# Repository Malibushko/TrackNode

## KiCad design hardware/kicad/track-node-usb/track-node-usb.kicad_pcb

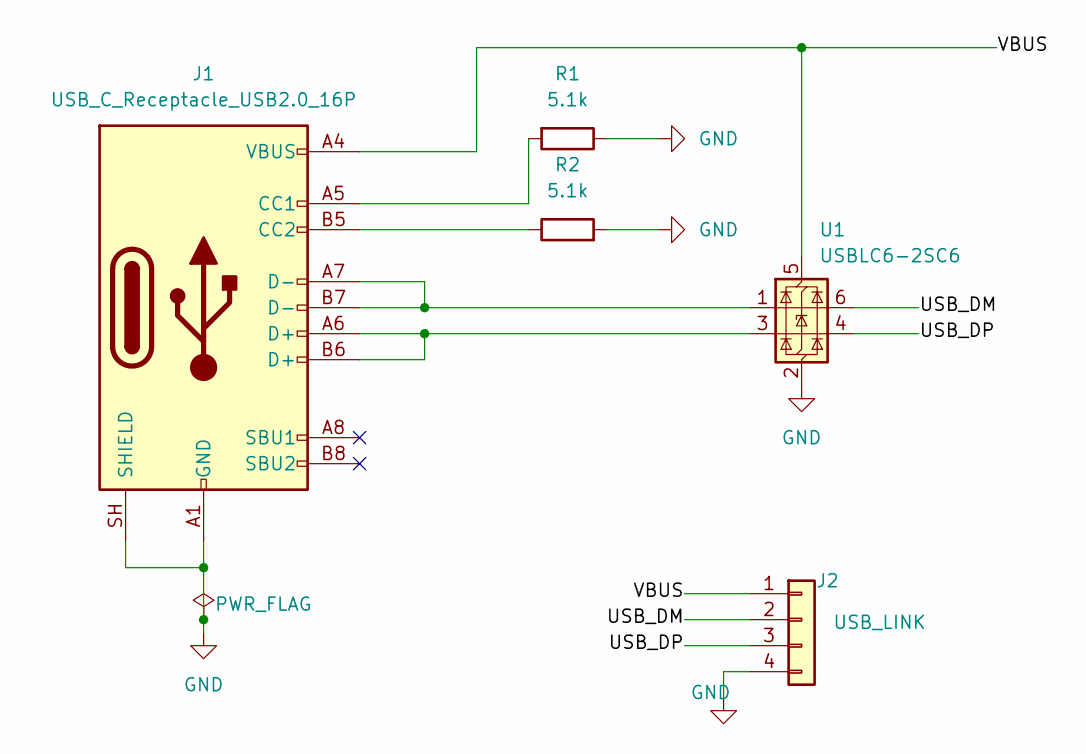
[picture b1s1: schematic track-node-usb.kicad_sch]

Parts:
J1: USB_C_Receptacle_USB2.0_16P; USB_C_Receptacle_HRO_TYPE-C-31-M-12_Edge; LCSC C165948
J2: USB_LINK; JST_SH_SM04B-SRSS-TB_1x04-1MP_P1.00mm_Horizontal; LCSC C160404
R1, R2: 5.1k; R_0603_1608Metric; LCSC C23186
U1: USBLC6-2SC6; SOT-23-6; LCSC C7519

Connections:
/USB_DM: J2.2, U1.6 (I/O1)
/USB_DP: J2.3, U1.4 (I/O2)
/VBUS: J1.A4 (VBUS), J1.A9 (VBUS), J1.B4 (VBUS), J1.B9 (VBUS), J2.1, U1.5 (VBUS)
GND: J1.A1 (GND), J1.A12 (GND), J1.B1 (GND), J1.B12 (GND), J1.SH (SHIELD), J2.4, R1.1, R2.2, U1.2 (GND)
unnamed: J1.A5 (CC1), R1.2
unnamed: J1.B5 (CC2), R2.1
unnamed: J1.A6 (D+), J1.B6 (D+), U1.3 (I/O2)
unnamed: J1.A7 (D-), J1.B7 (D-), U1.1 (I/O1)

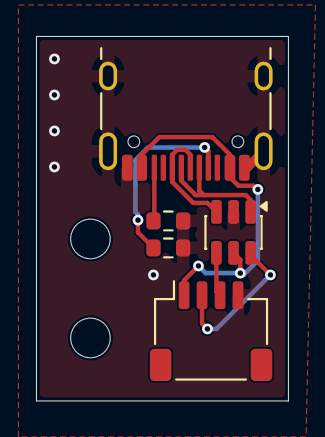
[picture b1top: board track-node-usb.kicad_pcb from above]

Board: 2 copper layers, 14.0 x 20.2 mm, 5 parts (0 on the bottom side), 8 nets.

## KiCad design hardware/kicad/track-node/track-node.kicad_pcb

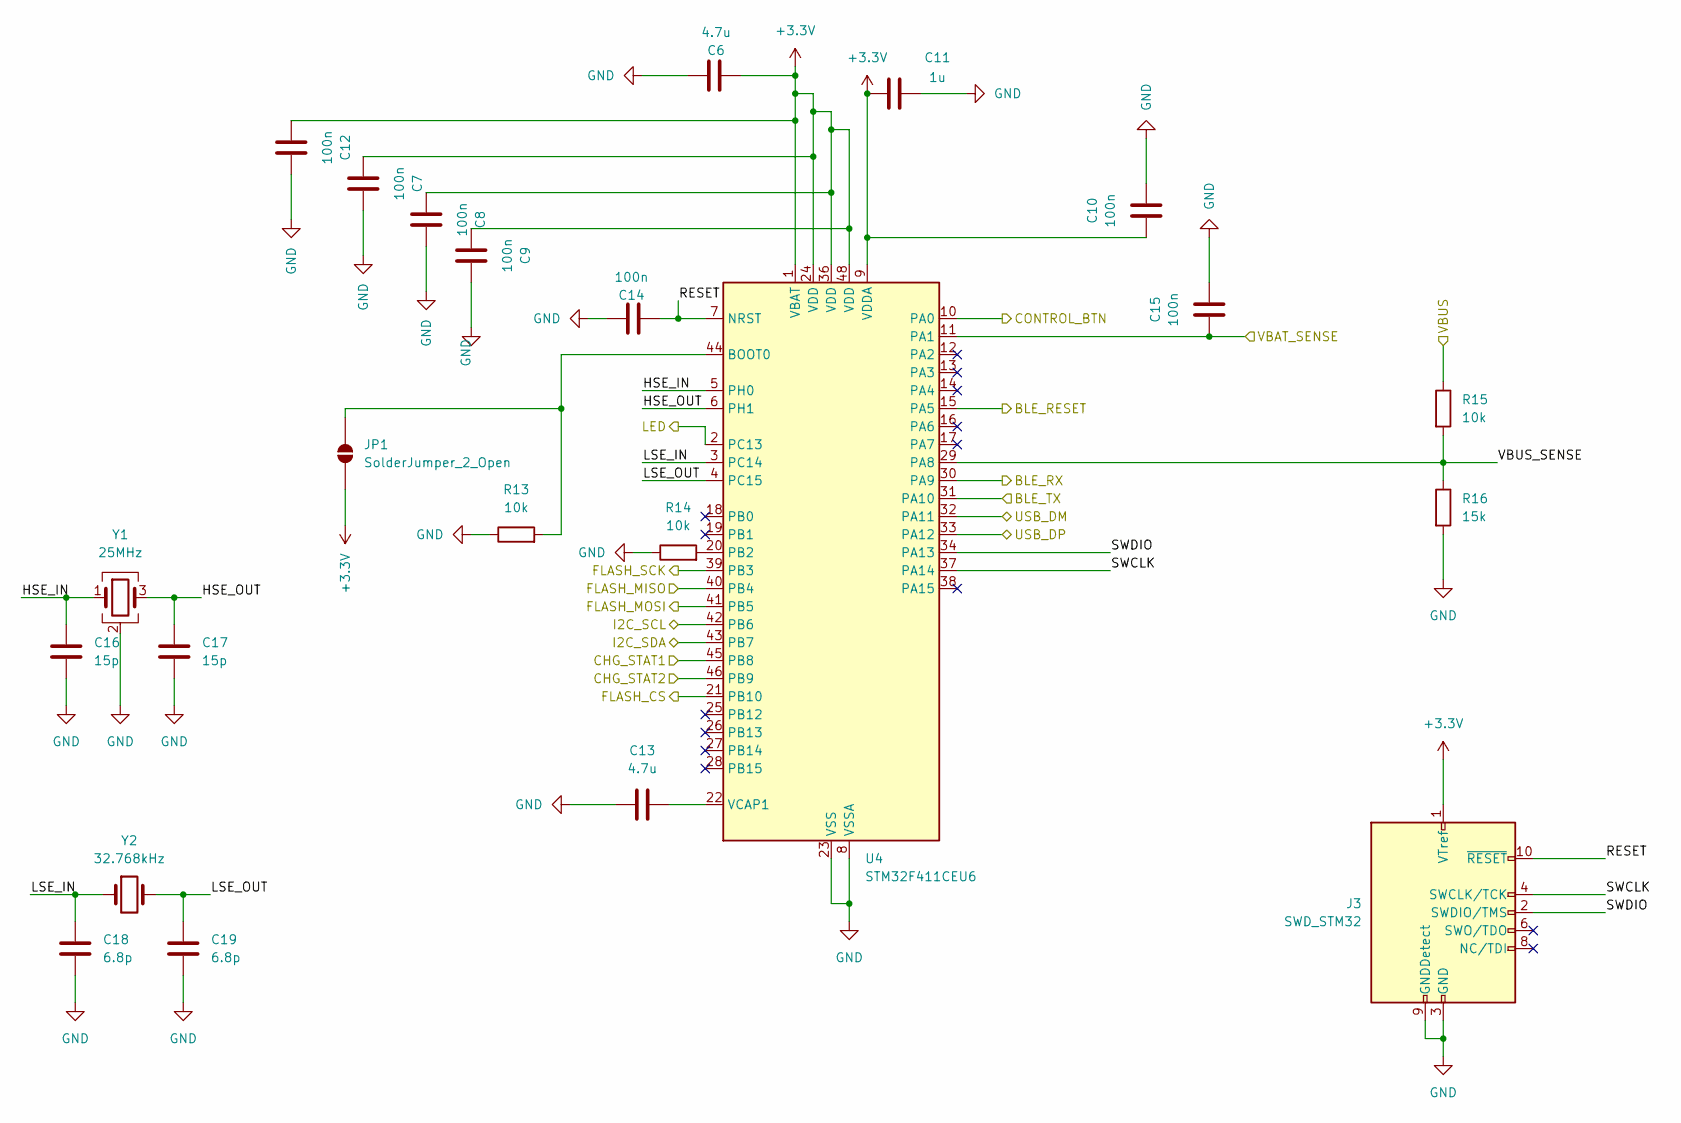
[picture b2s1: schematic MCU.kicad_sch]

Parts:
C6, C13: 4.7u; C_0603_1608Metric; LCSC C19666
C7, C8, C9, C10, C12, C14, C15: 100n; C_0603_1608Metric; LCSC C14663
C11: 1u; C_0603_1608Metric; LCSC C15849
C16, C17: 15p; C_0603_1608Metric; LCSC C1644
C18, C19: 6.8p; C_0603_1608Metric; LCSC C1679
J3: SWD_STM32; HDR-SMD_10P-P1.27-V-M-R2-C5-S1.27-LS5.5; LCSC C598540
JP1: SolderJumper_2_Open; SolderJumper-2_P1.3mm_Open_RoundedPad1.0x1.5mm
R13, R14, R15: 10k; R_0603_1608Metric; LCSC C25804
R16: 15k; R_0603_1608Metric; LCSC C22809
U4: STM32F411CEU6; QFN-48-1EP_7x7mm_P0.5mm_EP5.6x5.6mm; LCSC C60420
Y1: 25MHz; Crystal_SMD_3225-4Pin_3.2x2.5mm; LCSC C9006
Y2: 32.768kHz; Crystal_SMD_3215-2Pin_3.2x1.5mm; LCSC C276424

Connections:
+3.3V: C6.2, C7.2, C8.2, C9.2, C10.2, C11.2, C12.2, J3.1 (VTref), JP1.1 (A), U4.1 (VBAT), U4.9 (VDDA), U4.24 (VDD), U4.36 (VDD), U4.48 (VDD); also elsewhere on the board
/BLE/BLE_RESET: U4.15 (PA5); also elsewhere on the board
/BLE/BLE_RX: U4.30 (PA9); also elsewhere on the board
/BLE/BLE_TX: U4.31 (PA10); also elsewhere on the board
/MCU/CHG_STAT1: U4.45 (PB8); also elsewhere on the board
/MCU/CHG_STAT2: U4.46 (PB9); also elsewhere on the board
/MCU/CONTROL_BTN: U4.10 (PA0); also elsewhere on the board
/MCU/FLASH_CS: U4.21 (PB10); also elsewhere on the board
/MCU/FLASH_MISO: U4.40 (PB4); also elsewhere on the board
/MCU/FLASH_MOSI: U4.41 (PB5); also elsewhere on the board
/MCU/FLASH_SCK: U4.39 (PB3); also elsewhere on the board
/MCU/HSE_IN: C16.1, U4.5 (PH0), Y1.1
/MCU/HSE_OUT: C17.1, U4.6 (PH1), Y1.3
/MCU/I2C_SCL: U4.42 (PB6); also elsewhere on the board
/MCU/I2C_SDA: U4.43 (PB7); also elsewhere on the board
/MCU/LED: U4.2 (PC13); also elsewhere on the board
/MCU/LSE_IN: C18.1, U4.3 (PC14), Y2.1
/MCU/LSE_OUT: C19.1, U4.4 (PC15), Y2.2
/MCU/RESET: C14.2, J3.10 (~RESET), U4.7 (NRST)
/MCU/SWCLK: J3.4 (SWCLK/TCK), U4.37 (PA14)
/MCU/SWDIO: J3.2 (SWDIO/TMS), U4.34 (PA13)
/MCU/USB_DM: U4.32 (PA11); also elsewhere on the board
/MCU/USB_DP: U4.33 (PA12); also elsewhere on the board
/MCU/VBAT_SENSE: C15.2, U4.11 (PA1); also elsewhere on the board
/MCU/VBUS: R15.1; also elsewhere on the board
/MCU/VBUS_SENSE: R15.2, R16.1, U4.29 (PA8)
GND: C6.1, C7.1, C8.1, C9.1, C10.1, C11.1, C12.1, C13.1, C14.1, C15.1, C16.2, C17.2, C18.2, C19.2, J3.3 (GND), J3.5 (GND), J3.9 (GNDDetect), R13.1, R14.1, R16.2, U4.8 (VSSA), U4.23 (VSS), U4.35 (VSS), U4.47 (VSS), U4.49 (VSS), Y1.2 (G), Y1.4 (G); also elsewhere on the board
unnamed: JP1.2 (B), R13.2, U4.44 (BOOT0)
unnamed: R14.2, U4.20 (PB2)
unnamed: C13.2, U4.22 (VCAP1)

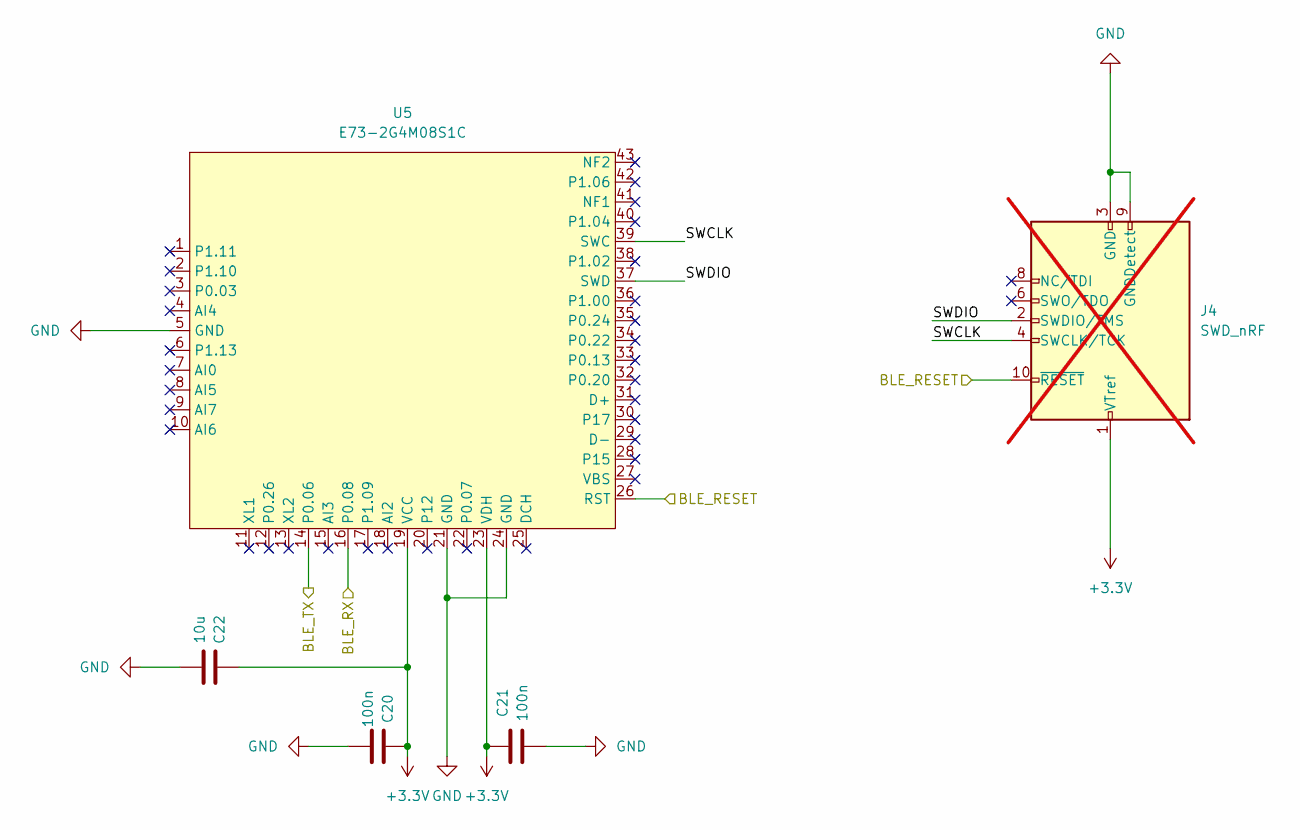
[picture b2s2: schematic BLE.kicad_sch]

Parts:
C20, C21: 100n; C_0603_1608Metric; LCSC C14663
C22: 10u; C_0603_1608Metric; LCSC C19702
J4: SWD_nRF; HDR-SMD_10P-P1.27-V-M-R2-C5-S1.27-LS5.5; not fitted
U5: E73-2G4M08S1C; WIRELM-SMD_E73-2G4M08S1C; MPN E73-2G4M08S1C; LCSC Part C356849

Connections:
+3.3V: C20.2, C21.2, C22.2, J4.1 (VTref), U5.19 (VCC), U5.23 (VDH); also elsewhere on the board
/BLE/BLE_RESET: J4.10 (~RESET), U5.26 (RST); also elsewhere on the board
/BLE/BLE_RX: U5.16 (P0.08); also elsewhere on the board
/BLE/BLE_TX: U5.14 (P0.06); also elsewhere on the board
/BLE/SWCLK: J4.4 (SWCLK/TCK), U5.39 (SWC)
/BLE/SWDIO: J4.2 (SWDIO/TMS), U5.37 (SWD)
GND: C20.1, C21.1, C22.1, J4.3 (GND), J4.5 (GND), J4.9 (GNDDetect), U5.5 (GND), U5.21 (GND), U5.24 (GND); also elsewhere on the board

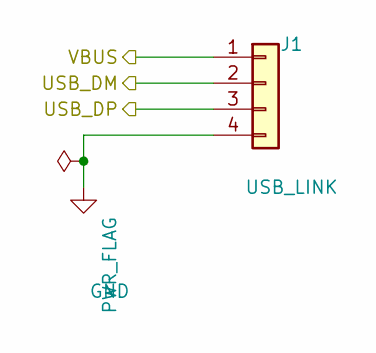
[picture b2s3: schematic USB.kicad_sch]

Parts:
J1: USB_LINK; JST_SH_SM04B-SRSS-TB_1x04-1MP_P1.00mm_Horizontal; LCSC C160404

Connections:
/MCU/USB_DM: J1.2; also elsewhere on the board
/MCU/USB_DP: J1.3; also elsewhere on the board
/MCU/VBUS: J1.1; also elsewhere on the board
GND: J1.4; also elsewhere on the board

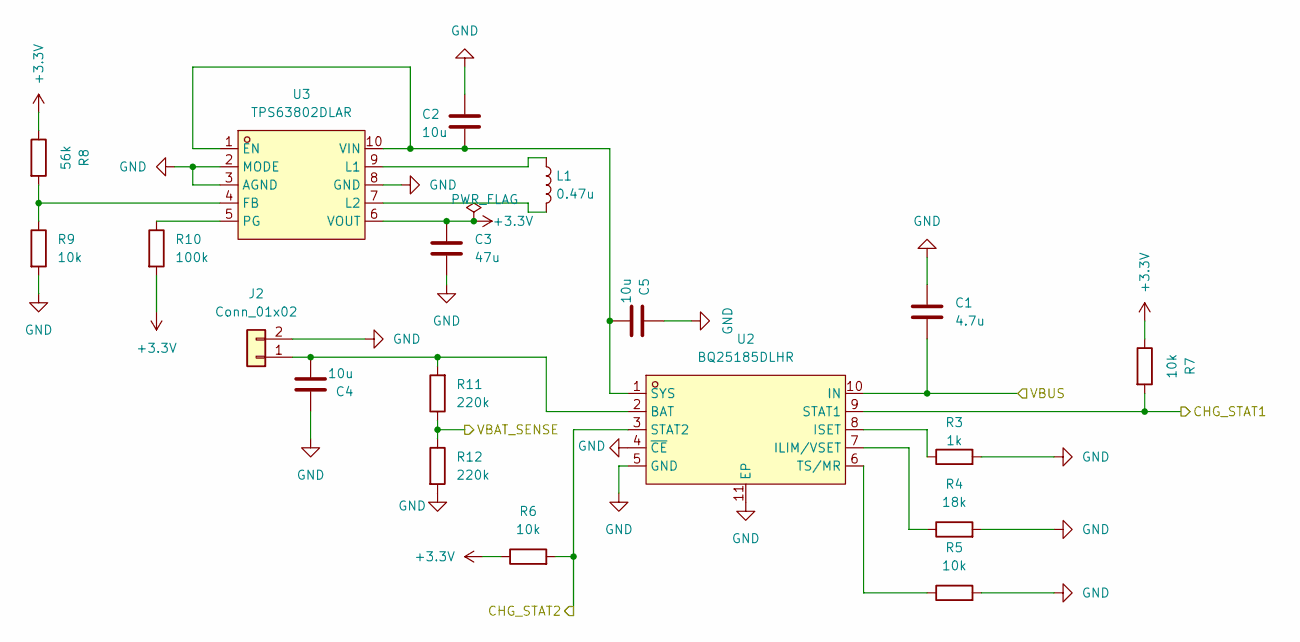
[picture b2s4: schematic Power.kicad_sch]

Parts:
C1: 4.7u; C_0603_1608Metric; LCSC C19666
C2, C4, C5: 10u; C_0603_1608Metric; LCSC C19702
C3: 47u; C_0805_2012Metric; LCSC C16780
J2: Conn_01x02; JST_PH_S2B-PH-SM4-TB_1x02-1MP_P2.00mm_Horizontal; LCSC C295747
L1: 0.47u; L_1008_2520Metric; LCSC C326159
R3: 1k; R_0603_1608Metric; LCSC C21190
R4: 18k; R_0603_1608Metric; LCSC C25810
R5, R6, R7, R9: 10k; R_0603_1608Metric; LCSC C25804
R8: 56k; R_0603_1608Metric; LCSC C23206
R10: 100k; R_0603_1608Metric; LCSC C25803
R11, R12: 220k; R_0603_1608Metric; LCSC C22961
U2: BQ25185DLHR; WSON-10_L2.2-W2.0-P0.40-BL-EP_TI_DLH0010A; MPN BQ25185DLHR; LCSC Part C19725033
U3: TPS63802DLAR; VSON-10_L3.0-W2.0-P0.50-TL; MPN TPS63802DLAR; LCSC Part C2845237

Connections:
+3.3V: C3.1, R6.1, R7.1, R8.1, R10.2, U3.6 (VOUT); also elsewhere on the board
/MCU/CHG_STAT1: R7.2, U2.9 (STAT1); also elsewhere on the board
/MCU/CHG_STAT2: R6.2, U2.3 (STAT2); also elsewhere on the board
/MCU/VBAT_SENSE: R11.1, R12.1; also elsewhere on the board
/MCU/VBUS: C1.2, U2.10 (IN); also elsewhere on the board
GND: C1.1, C2.1, C3.2, C4.1, C5.1, J2.2, R3.2, R4.2, R5.2, R9.2, R12.2, U2.4 (~CE), U2.5 (GND), U2.11 (EP), U3.2 (MODE), U3.3 (AGND), U3.8 (GND); also elsewhere on the board
unnamed: C4.2, J2.1, R11.2, U2.2 (BAT)
unnamed: R4.1, U2.7 (ILIM/VSET)
unnamed: R3.1, U2.8 (ISET)
unnamed: C2.2, C5.2, U2.1 (SYS), U3.1 (EN), U3.10 (VIN)
unnamed: R5.1, U2.6 (TS/MR)
unnamed: R8.2, R9.1, U3.4 (FB)
unnamed: L1.1, U3.9 (L1)
unnamed: L1.2, U3.7 (L2)
unnamed: R10.1, U3.5 (PG)

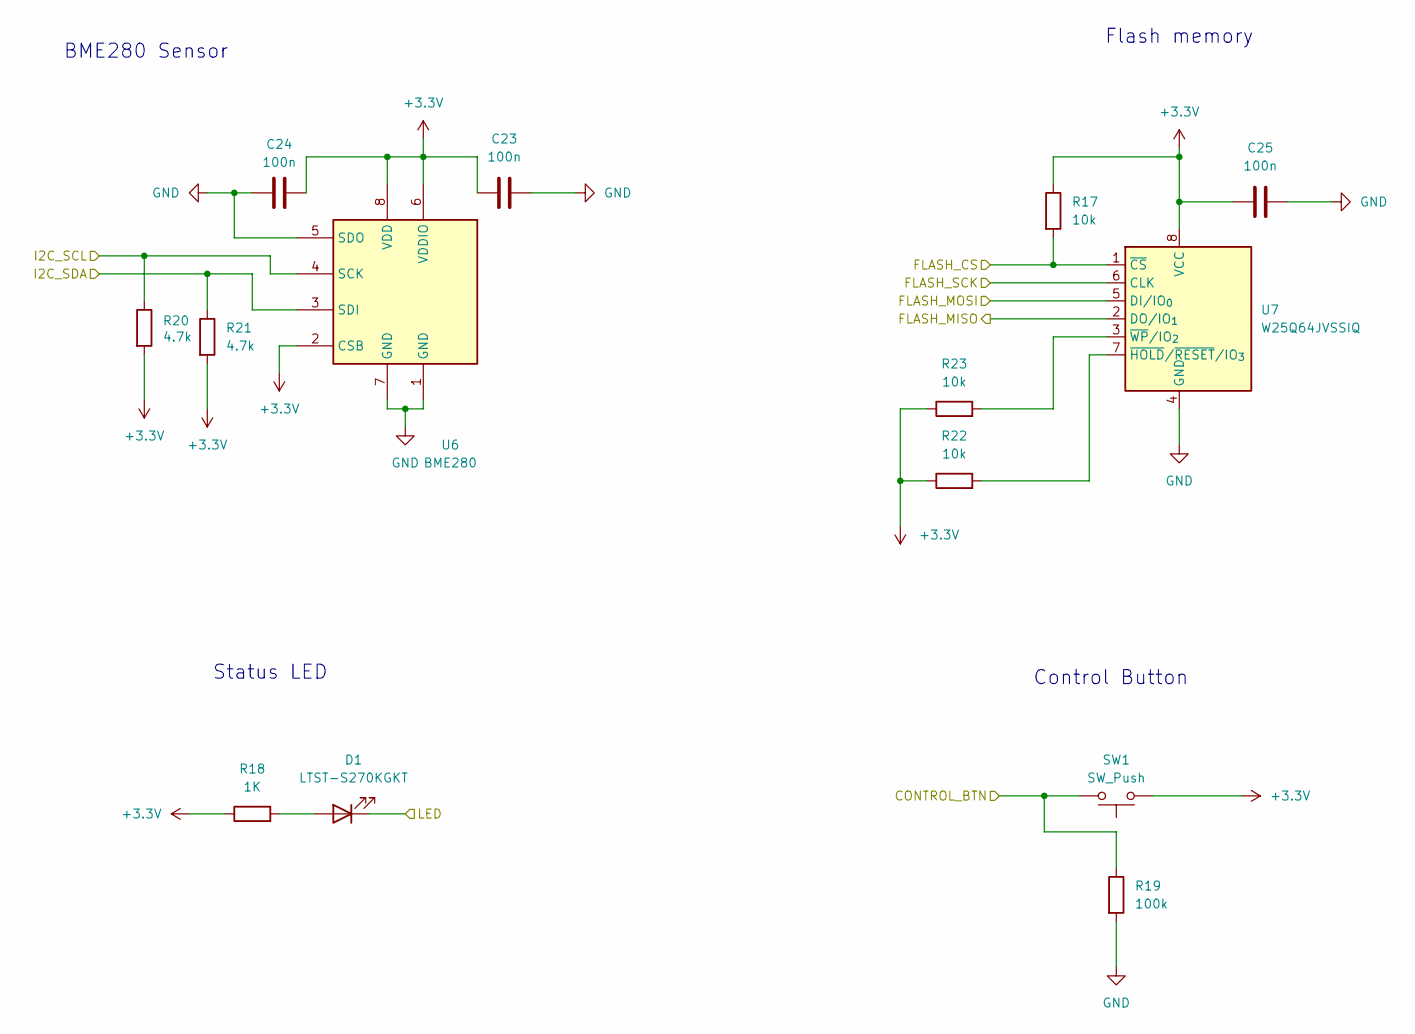
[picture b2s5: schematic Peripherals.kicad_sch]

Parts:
C23, C24, C25: 100n; C_0603_1608Metric; LCSC C14663
D1: LTST-S270KGKT; LED-SMD_L1.7-W0.6-RD; LCSC C125113
R17, R22, R23: 10k; R_0603_1608Metric; LCSC C25804
R18: 1K; R_0603_1608Metric; LCSC C21190
R19: 100k; R_0603_1608Metric; LCSC C25803
R20, R21: 4.7k; R_0603_1608Metric; LCSC C23162
SW1: SW_Push; SW-SMD_4P-L5.1-W5.1-P3.70-LS6.5-TL_H1.5; LCSC C318884
U6: BME280; Bosch_LGA-8_2.5x2.5mm_P0.65mm_ClockwisePinNumbering; LCSC C92489
U7: W25Q64JVSSIQ; SOIC-8_5.3x5.3mm_P1.27mm; LCSC C179171

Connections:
+3.3V: C23.1, C24.1, C25.1, R17.1, R18.1, R20.2, R21.2, R22.1, R23.1, SW1.1, U6.2 (CSB), U6.6 (VDDIO), U6.8 (VDD), U7.8 (VCC); also elsewhere on the board
/MCU/CONTROL_BTN: R19.1, SW1.2; also elsewhere on the board
/MCU/FLASH_CS: R17.2, U7.1 (~CS); also elsewhere on the board
/MCU/FLASH_MISO: U7.2 (DO/IO_{1}); also elsewhere on the board
/MCU/FLASH_MOSI: U7.5 (DI/IO_{0}); also elsewhere on the board
/MCU/FLASH_SCK: U7.6 (CLK); also elsewhere on the board
/MCU/I2C_SCL: R20.1, U6.4 (SCK); also elsewhere on the board
/MCU/I2C_SDA: R21.1, U6.3 (SDI); also elsewhere on the board
/MCU/LED: D1.1 (K); also elsewhere on the board
GND: C23.2, C24.2, C25.2, R19.2, U6.1 (GND), U6.5 (SDO), U6.7 (GND), U7.4 (GND); also elsewhere on the board
unnamed: D1.2 (A), R18.2
unnamed: R22.2, U7.7 (~HOLD/~RESET/IO_{3})
unnamed: R23.2, U7.3 (~WP/IO_{2})

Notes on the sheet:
Control Button
Status LED
BME280 Sensor
Flash memory

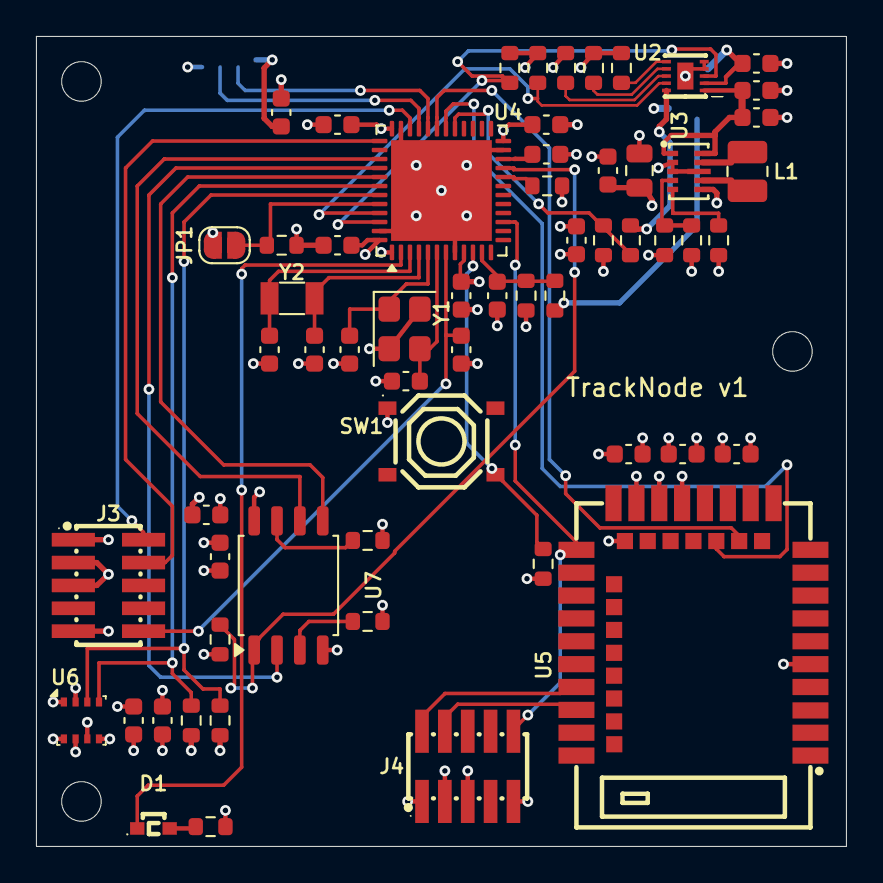
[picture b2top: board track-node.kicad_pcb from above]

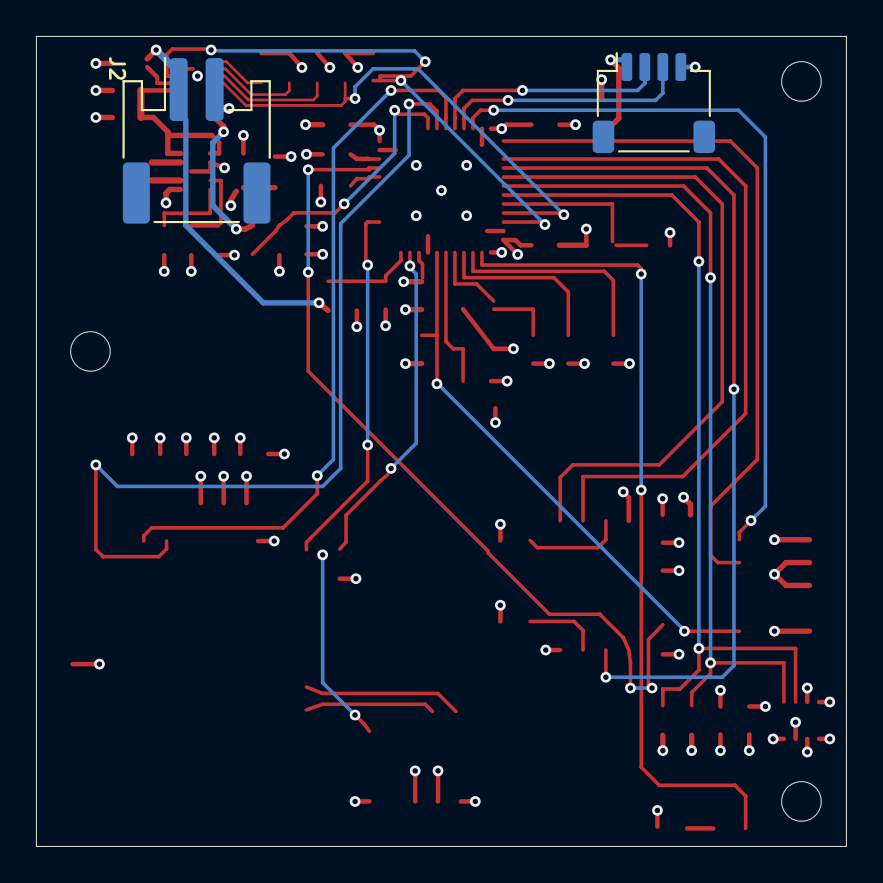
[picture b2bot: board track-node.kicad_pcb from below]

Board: 4 copper layers, 45.0 x 45.0 mm, 62 parts (2 on the bottom side), 44 nets.
